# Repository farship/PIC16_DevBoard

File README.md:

This is based on the university one, and I don't actually know if it works.

They used PIC16F84A for this devlopment board. https://ww1.microchip.com/downloads/en/devicedoc/35007b.pdf

This was made almost entirely to see how easy it would be.

Conclusion: It was pretty easy after I worked out what the switch was doing.

One major improvement to the original design by the uni, was removing the need for a ground plane, this makes it cheaper and easier to manufacture.

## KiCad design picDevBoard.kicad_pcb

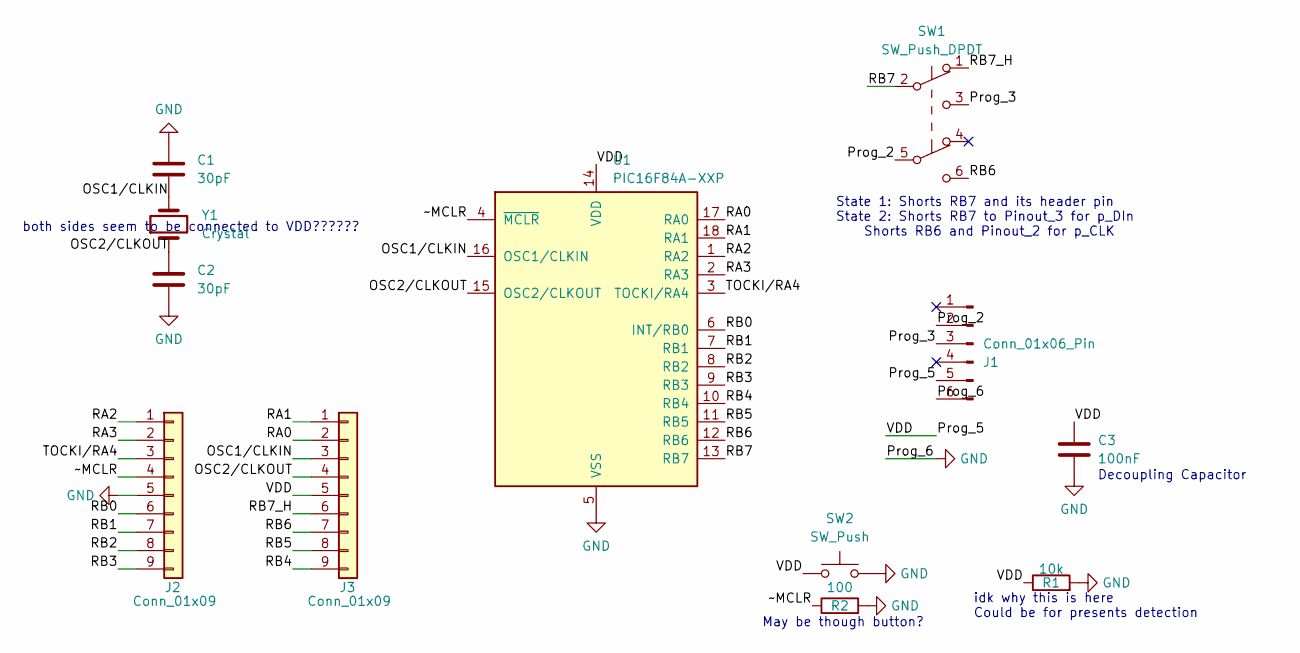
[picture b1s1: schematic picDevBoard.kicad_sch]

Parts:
C1, C2: 30pF; C_0805_2012Metric_Pad1.18x1.45mm_HandSolder
C3: 100nF; C_0805_2012Metric_Pad1.18x1.45mm_HandSolder
J1: Conn_01x06_Pin; PinHeader_1x06_P2.54mm_Horizontal
J2, J3: Conn_01x09; PinHeader_1x09_P2.54mm_Vertical
R1: 10k; R_0603_1608Metric_Pad0.98x0.95mm_HandSolder
R2: 100; R_0603_1608Metric_Pad0.98x0.95mm_HandSolder
SW1: SW_Push_DPDT; SW_CuK_JS202011CQN_DPDT_Straight
SW2: SW_Push; SW_PUSH_6mm
U1: PIC16F84A-XXP; DIP-18_W7.62mm_Socket
Y1: Crystal; SOIC-2

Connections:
/OSC1/CLKIN: C1.2, J3.3, U1.16 (OSC1/CLKIN), Y1.2
/OSC2/CLKOUT: C2.1, J3.4, U1.15 (OSC2/CLKOUT), Y1.1
/Prog_2: J1.2, SW1.5 (B)
/Prog_3: J1.3, SW1.3 (C)
/Prog_5: C3.1, J1.5, J3.5, R1.1, SW2.1, U1.14 (VDD)
/RA0: J3.2, U1.17 (RA0)
/RA1: J3.1, U1.18 (RA1)
/RA2: J2.1, U1.1 (RA2)
/RA3: J2.2, U1.2 (RA3)
/RB0: J2.6, U1.6 (INT/RB0)
/RB1: J2.7, U1.7 (RB1)
/RB2: J2.8, U1.8 (RB2)
/RB3: J2.9, U1.9 (RB3)
/RB4: J3.9, U1.10 (RB4)
/RB5: J3.8, U1.11 (RB5)
/RB6: J3.7, SW1.6 (C), U1.12 (RB6)
/RB7: SW1.2 (B), U1.13 (RB7)
/RB7_H: J3.6, SW1.1 (A)
/TOCKI/RA4: J2.3, U1.3 (TOCKI/RA4)
/~MCLR: J2.4, R2.1, U1.4 (~MCLR)
GND: C1.1, C2.2, C3.2, J1.6, J2.5, R1.2, R2.2, SW2.2, U1.5 (VSS)

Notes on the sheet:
Decoupling Capacitor
State 1: Shorts RB7 and its header pin State 2: Shorts RB7 to Pinout_3 for p_DIn Shorts RB6 and Pinout_2 for p_CLK
both sides seem to be connected to VDD??????
May be though button?
idk why this is here Could be for presents detection

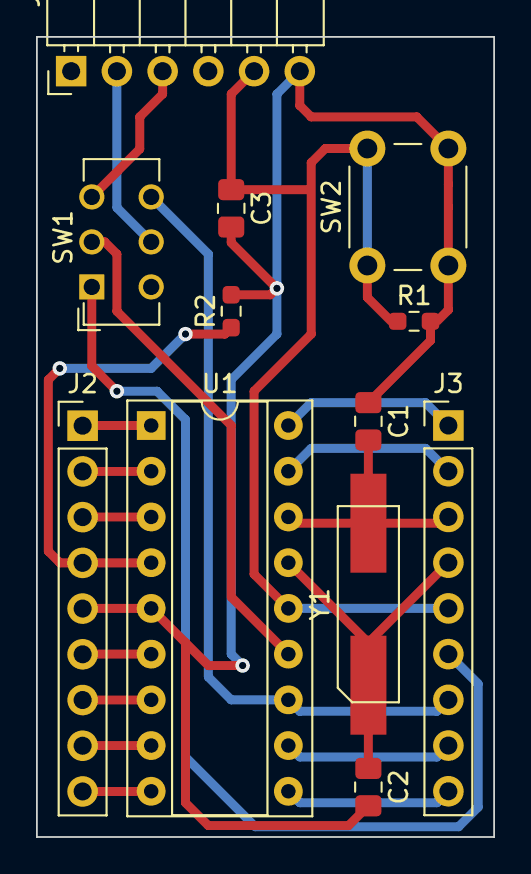
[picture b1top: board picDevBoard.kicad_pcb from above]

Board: 2 copper layers, 25.4 x 44.4 mm, 12 parts (0 on the bottom side), 21 nets.

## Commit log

2024-01-22 Uploaded V1
2024-01-22 Update README.md
    spacing
2024-01-22 Update README.md
    added link to datasheet
